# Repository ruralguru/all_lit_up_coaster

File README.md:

# all_lit_up_coaster
LED coaster design,

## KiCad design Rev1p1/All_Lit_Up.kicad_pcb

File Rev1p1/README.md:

# all_lit_up_coaster
LED coaster design.
Created in conjunction with Mad Physist.
Alternating LED design using 555 timer, powered by 4x AAA, Aluminum Can Trigger.
Some moderate soldering required.

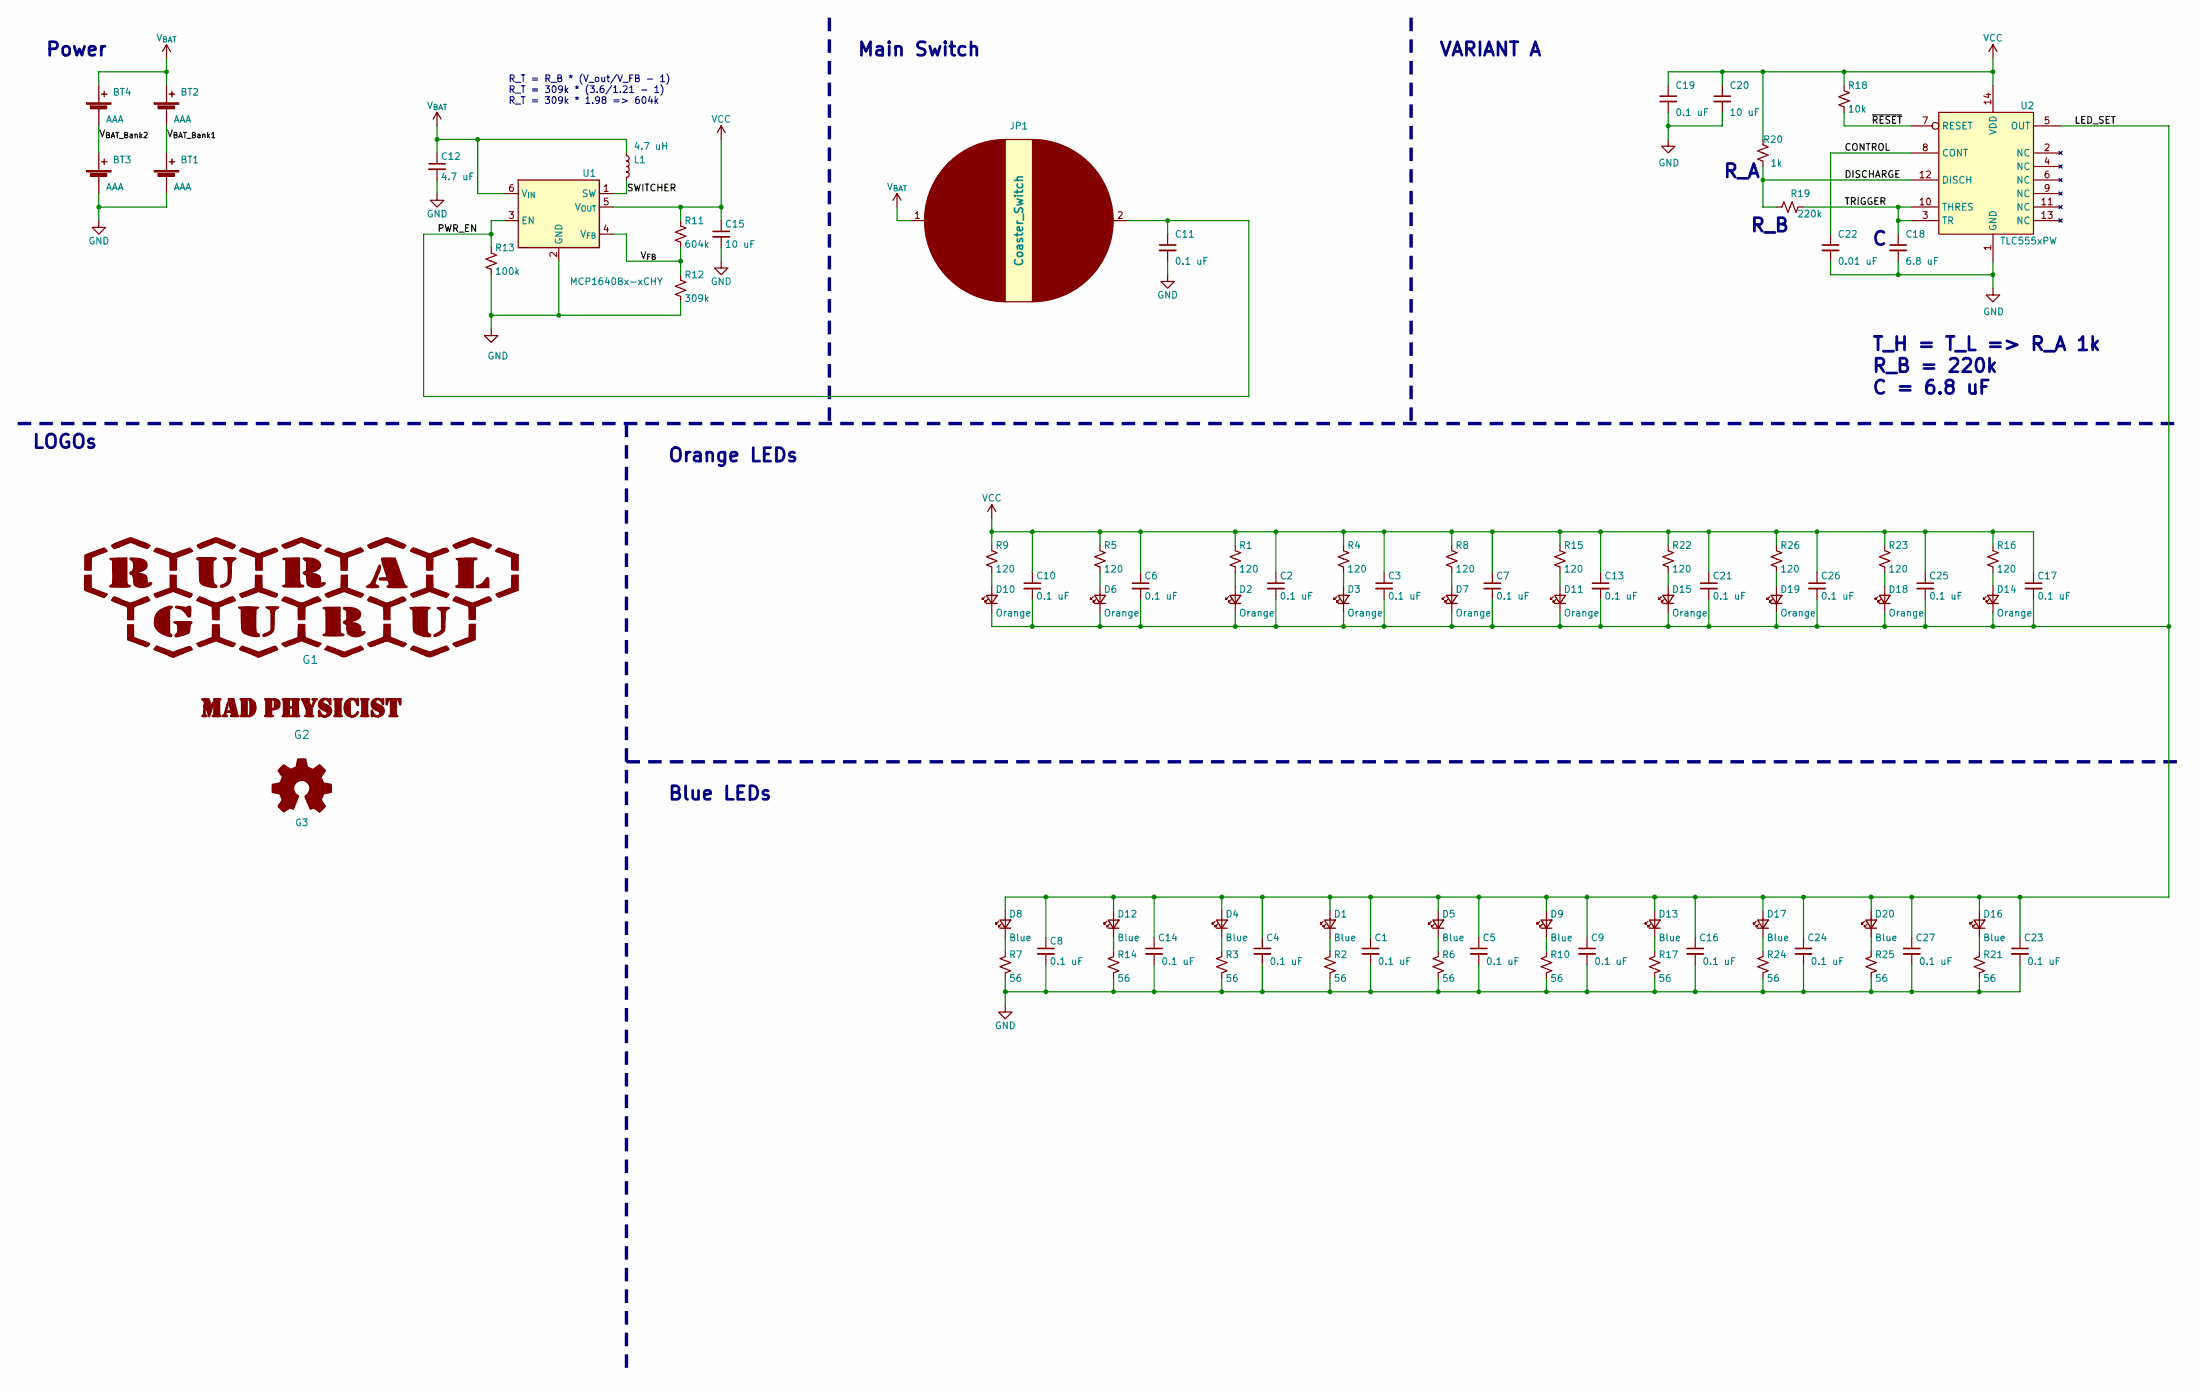
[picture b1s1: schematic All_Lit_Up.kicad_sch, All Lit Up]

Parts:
BT1, BT2, BT3, BT4: AAA; ERW_Battery_Keystone_55(x2)_AAAA; MPN 55 (x2)
C1, C2, C3, C4, C5, C6, C7, C8, C9, C10, C11, C13, C14, C16, C17, C19, C21, C23, C24, C25, C26, C27: 0.1 uF; C_0603_1608Metric; MPN CL10B104KA8NNNC
C12: 4.7 uF; C_0603_1608Metric; MPN GRM188Z71A475ME15D
C15, C20: 10 uF; C_0603_1608Metric; MPN GRM188Z71A106KA73D
C18: 6.8 uF; C_0603_1608Metric; MPN C1608X7S0J685K080AC
C22: 0.01 uF; C_0603_1608Metric; MPN C1608C0G1E103J080AA
D1, D4, D5, D8, D9, D12, D13, D16, D17, D20: Blue; LED_0603_1608Metric; MPN E1221NB--05D000814U1930
D2, D3, D6, D7, D10, D11, D14, D15, D18, D19: Orange; LED_0603_1608Metric; MPN B1911UD--20D001014U1930
G1: LOGO; RuralguruProjects_HEX_2000
G2: Phillip_LOGO; PJ_LOGO_1p5l
G3: Logo_Open_Hardware_Small; OSHW-Symbol_6.7x6mm_SilkScreen
JP1: Coaster_Switch; Coaster_SW
L1: 4.7 uH; L_VLCF4020T; MPN VLCF4020T-4R7N1R2
R1, R4, R5, R8, R9, R15, R16, R22, R23, R26: 120; R_0603_1608Metric; MPN RT0603FRE07120RL
R2, R3, R6, R7, R10, R14, R17, R21, R24, R25: 56; R_0603_1608Metric; MPN RT0603FRE0756RL
R11: 604k; R_0603_1608Metric; MPN RMCF0603FT604K
R12: 309k; R_0603_1608Metric; MPN RMCF0603FT309K
R13: 100k; R_0603_1608Metric; MPN ERJ-3EKF1003V
R18: 10k; R_0603_1608Metric; MPN CRGCQ0603F10K
R19: 220k; R_0603_1608Metric; MPN RMCF0603FT220K
R20: 1k; R_0603_1608Metric; MPN RT0603FRE131KL
U1: MCP1640Bx-xCHY; SOT-23-6; MPN MCP1640BT-I/CHY
U2: TLC555xPW; TSSOP-14_4.4x5mm_P0.65mm; MPN TLC555CPWR

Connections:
/CONTROL: C22.1, U2.8 (CONT)
/DISCHARGE: R19.2, R20.1, U2.12 (DISCH)
/LED_SET: C1.1, C2.2, C3.2, C4.1, C5.1, C6.2, C7.2, C8.1, C9.1, C10.2, C13.2, C14.1, C16.1, C17.2, C21.2, C23.1, C24.1, C25.2, C26.2, C27.1, D1.2 (A), D2.1 (K), D3.1 (K), D4.2 (A), D5.2 (A), D6.1 (K), D7.1 (K), D8.2 (A), D9.2 (A), D10.1 (K), D11.1 (K), D12.2 (A), D13.2 (A), D14.1 (K), D15.1 (K), D16.2 (A), D17.2 (A), D18.1 (K), D19.1 (K), D20.2 (A), U2.5 (OUT)
/PWR_EN: C11.1, JP1.2 (B), R13.1, U1.3 (EN)
/SWITCHER: L1.2, U1.1 (SW)
/TRIGGER: C18.1, R19.1, U2.3 (TR), U2.10 (THRES)
/V_{BAT_Bank1}: BT1.1 (+), BT2.2 (-)
/V_{BAT_Bank2}: BT3.1 (+), BT4.2 (-)
/V_{FB}: R11.2, R12.1, U1.4 (V_{FB})
/~RESET: R18.2, U2.7 (RESET)
GND: BT1.2 (-), BT3.2 (-), C1.2, C4.2, C5.2, C8.2, C9.2, C11.2, C12.2, C14.2, C15.2, C16.2, C18.2, C19.2, C20.2, C22.2, C23.2, C24.2, C27.2, R2.2, R3.2, R6.2, R7.2, R10.2, R12.2, R13.2, R14.2, R17.2, R21.2, R24.2, R25.2, U1.2 (GND), U2.1 (GND)
unnamed: D1.1 (K), R2.1
unnamed: D2.2 (A), R1.2
unnamed: D3.2 (A), R4.2
unnamed: D4.1 (K), R3.1
unnamed: D5.1 (K), R6.1
unnamed: D6.2 (A), R5.2
unnamed: D7.2 (A), R8.2
unnamed: D8.1 (K), R7.1
unnamed: D9.1 (K), R10.1
unnamed: D10.2 (A), R9.2
unnamed: D11.2 (A), R15.2
unnamed: D12.1 (K), R14.1
unnamed: D13.1 (K), R17.1
unnamed: D14.2 (A), R16.2
unnamed: D15.2 (A), R22.2
unnamed: D16.1 (K), R21.1
unnamed: D17.1 (K), R24.1
unnamed: D18.2 (A), R23.2
unnamed: D19.2 (A), R26.2
unnamed: D20.1 (K), R25.1
VCC: C2.1, C3.1, C6.1, C7.1, C10.1, C13.1, C15.1, C17.1, C19.1, C20.1, C21.1, C25.1, C26.1, R1.1, R4.1, R5.1, R8.1, R9.1, R11.1, R15.1, R16.1, R18.1, R20.2, R22.1, R23.1, R26.1, U1.5 (V_{OUT}), U2.14 (VDD)
V_{BAT}: BT2.1 (+), BT4.1 (+), C12.1, JP1.1 (A), L1.1, U1.6 (V_{IN})

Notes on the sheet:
VARIANT A
LOGOs
Blue LEDs
Main Switch
T_H = T_L => R_A 1k R_B = 220k C = 6.8 uF
R_A
R_B
Power
R_T = R_B * (V_out/V_FB - 1) R_T = 309k * (3.6/1.21 - 1) R_T = 309k * 1.98 => 604k
Orange LEDs

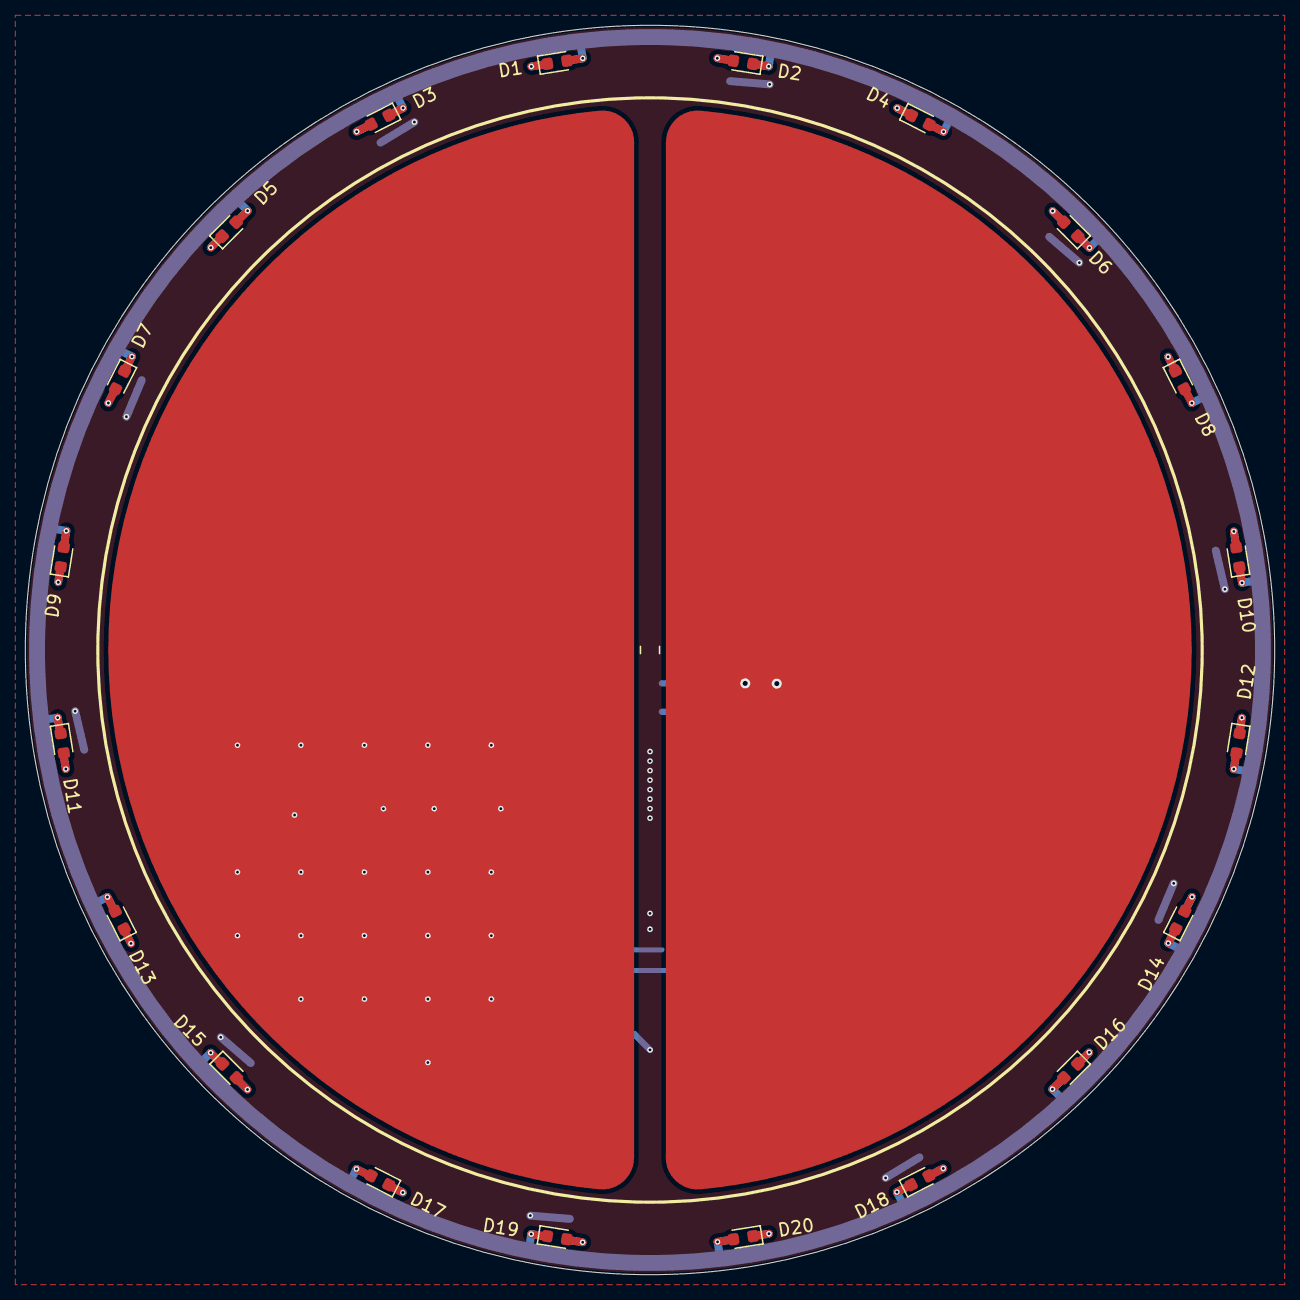
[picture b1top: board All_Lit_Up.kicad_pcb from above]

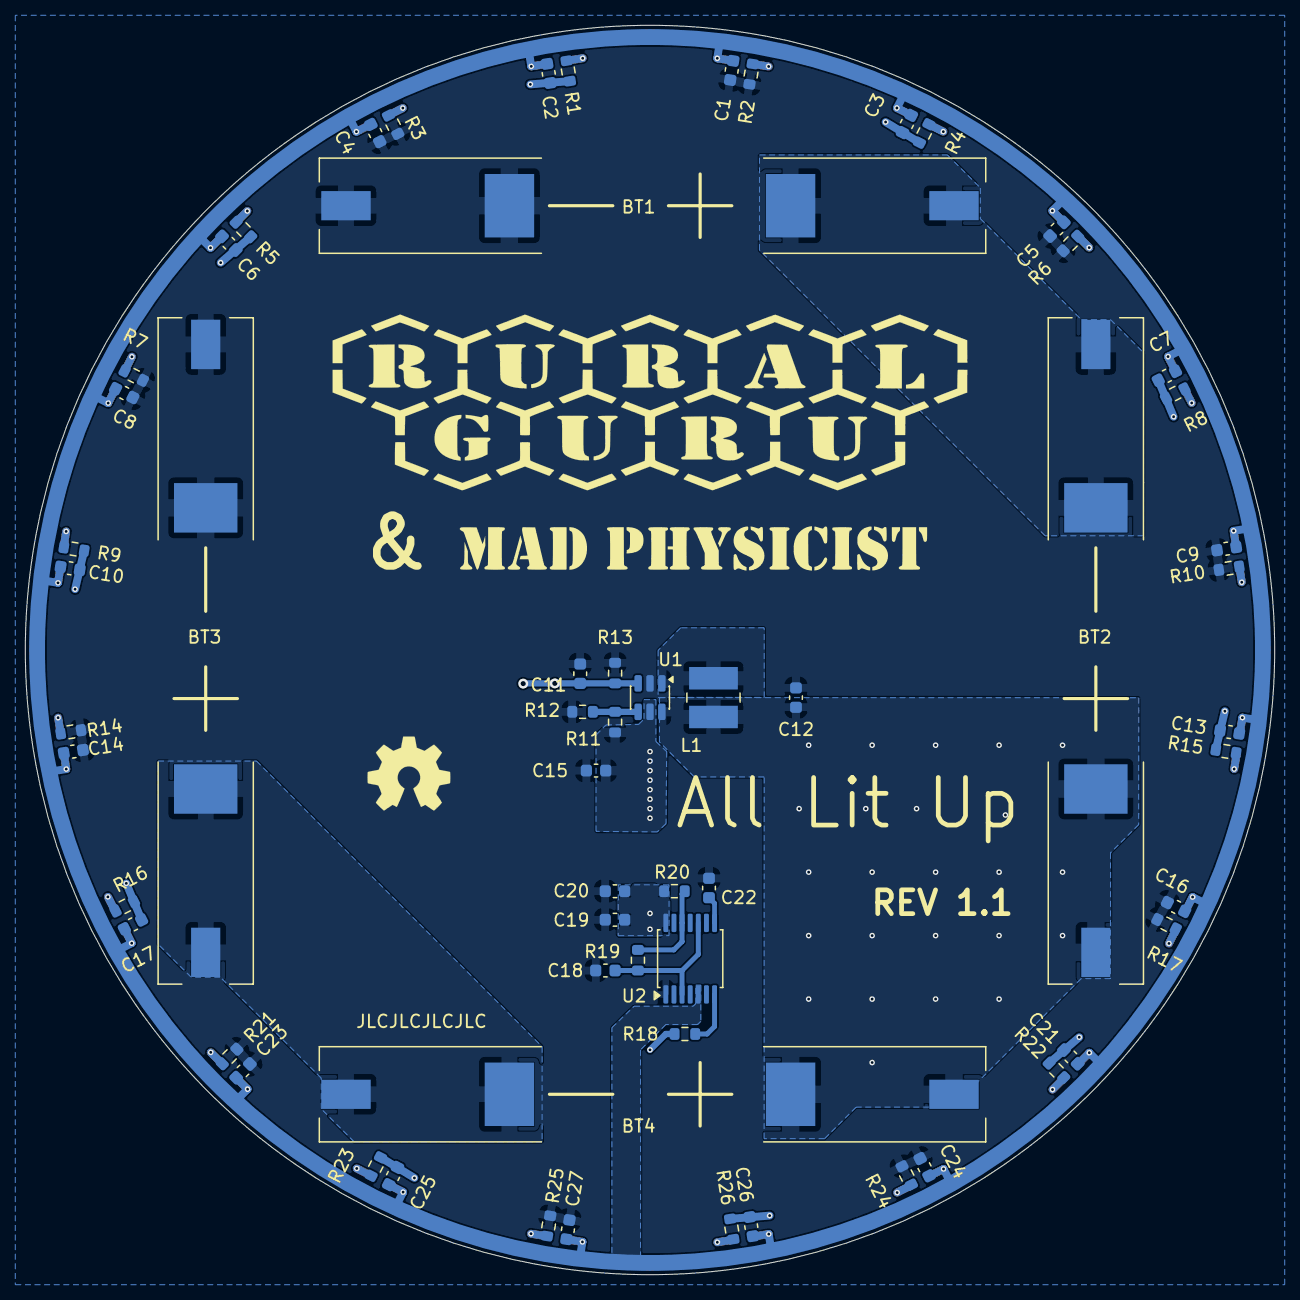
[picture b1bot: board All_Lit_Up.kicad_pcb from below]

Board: 2 copper layers, 100.0 x 100.0 mm, 84 parts (63 on the bottom side), 33 nets.

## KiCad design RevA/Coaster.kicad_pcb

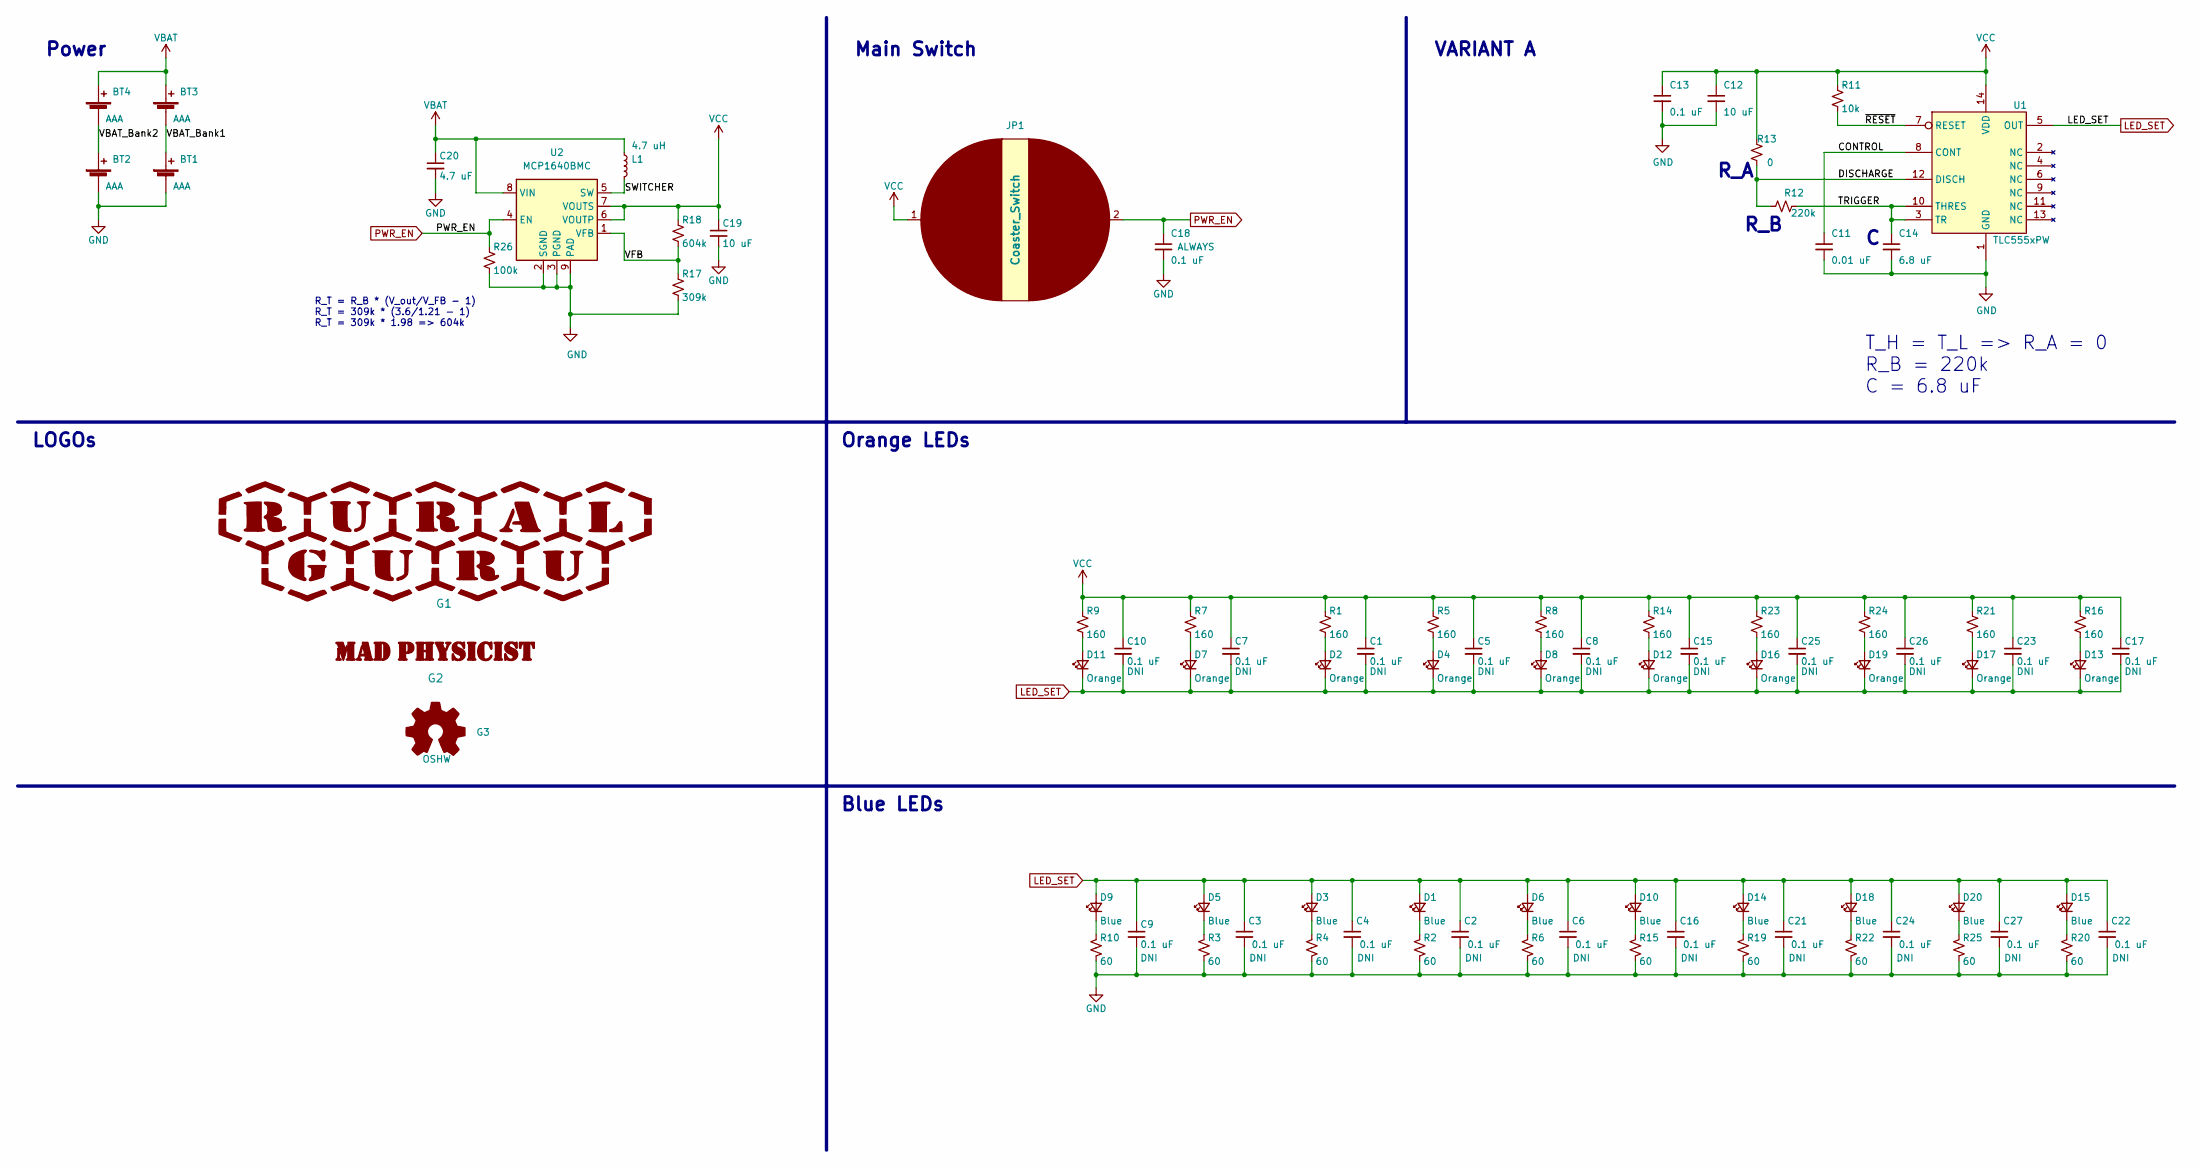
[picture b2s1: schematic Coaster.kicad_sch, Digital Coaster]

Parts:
BT1, BT2, BT3, BT4: AAA; ERW_Battery_Keystone_55(x2)_AAAA; MPN 55
C1, C2, C3, C4, C5, C6, C7, C8, C9, C10, C13, C15, C16, C17, C18, C21, C22, C23, C24, C25, C26, C27: 0.1 uF; C_0603_1608Metric; MPN C0603C104K4NACAUTO
C11: 0.01 uF; C_0603_1608Metric; MPN GRM1885C1H103JA01D
C12: 10 uF; C_0603_1608Metric; MPN CL10B106MQ8NRNC
C14: 6.8 uF; C_0603_1608Metric; MPN C1608X7S0J685M080AC
C19: 10 uF; C_0603_1608Metric; MPN CL10B475KQ8NQNC
C20: 4.7 uF; C_0603_1608Metric; MPN CL10B475KQ8NQNC
D1, D3, D5, D6, D9, D10, D14, D15, D18, D20: Blue; LED_0603_1608Metric; MPN APT1608VBC/D
D2, D4, D7, D8, D11, D12, D13, D16, D17, D19: Orange; LED_0603_1608Metric; MPN AP1608SECK
G1: LOGO; RuralguruProjects_HEX_2000
G2: LOGO; OSHW-LOGO-M
G3: OSHW; OSHW-LOGO-M
JP1: Coaster_Switch; Coaster_SW
L1: 4.7 uH; VLCF4020T-4R7N1R2; MPN 1239AS-H-2R2M=P2
R1, R5, R7, R8, R9, R14, R16, R21, R23, R24: 160; R_0603_1608Metric; MPN RT0805FRE07160RL
R2, R3, R4, R6, R10, R15, R19, R20, R22, R25: 60; R_0603_1608Metric; MPN RT0603FRE0760R4L
R11: 10k; R_0603_1608Metric; MPN RT0603FRE1310KL
R12: 220k; R_0603_1608Metric; MPN RT0603DRE07220KL
R13: 0; R_0603_1608Metric; MPN RC0603FR-070RL
R17: 309k; R_0603_1608Metric; MPN RT0603DRE07100KL
R18: 604k; R_0603_1608Metric; MPN RT0603DRE07357KL
R26: 100k; R_0603_1608Metric; MPN RT0603DRE07100KL
U1: TLC555xPW; TSSOP-14_4.4x5mm_P0.65mm; MPN TLC555CPWRG4
U2: MCP1640BMC; DFN-8-1EP_3x2mm_P0.5mm_EP1.75x1.45mm

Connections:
/CONTROL: C11.1, U1.8 (CONT)
/DISCHARGE: R12.2, R13.1, U1.12 (DISCH)
/SWITCHER: L1.2, U2.5 (SW)
/TRIGGER: C14.1, R12.1, U1.3 (TR), U1.10 (THRES)
/VBAT_Bank1: BT1.1 (+), BT3.2 (-)
/VBAT_Bank2: BT2.1 (+), BT4.2 (-)
/VFB: R17.1, R18.2, U2.1 (VFB)
/~RESET: R11.2, U1.7 (RESET)
GND: BT1.2 (-), BT2.2 (-), C2.2, C3.2, C4.2, C6.2, C9.2, C11.2, C12.2, C13.2, C14.2, C16.2, C18.2, C19.2, C20.2, C21.2, C22.2, C24.2, C27.2, R2.2, R3.2, R4.2, R6.2, R10.2, R15.2, R17.2, R19.2, R20.2, R22.2, R25.2, R26.2, U1.1 (GND), U2.2 (SGND), U2.3 (PGND), U2.9 (PAD)
LED_SET: C1.2, C2.1, C3.1, C4.1, C5.2, C6.1, C7.2, C8.2, C9.1, C10.2, C15.2, C16.1, C17.2, C21.1, C22.1, C23.2, C24.1, C25.2, C26.2, C27.1, D1.2 (A), D2.1 (K), D3.2 (A), D4.1 (K), D5.2 (A), D6.2 (A), D7.1 (K), D8.1 (K), D9.2 (A), D10.2 (A), D11.1 (K), D12.1 (K), D13.1 (K), D14.2 (A), D15.2 (A), D16.1 (K), D17.1 (K), D18.2 (A), D19.1 (K), D20.2 (A), U1.5 (OUT)
unnamed: D1.1 (K), R2.1
unnamed: D2.2 (A), R1.2
unnamed: D3.1 (K), R4.1
unnamed: D4.2 (A), R5.2
unnamed: D5.1 (K), R3.1
unnamed: D6.1 (K), R6.1
unnamed: D7.2 (A), R7.2
unnamed: D8.2 (A), R8.2
unnamed: D9.1 (K), R10.1
unnamed: D10.1 (K), R15.1
unnamed: D11.2 (A), R9.2
unnamed: D12.2 (A), R14.2
unnamed: D13.2 (A), R16.2
unnamed: D14.1 (K), R19.1
unnamed: D15.1 (K), R20.1
unnamed: D16.2 (A), R23.2
unnamed: D17.2 (A), R21.2
unnamed: D18.1 (K), R22.1
unnamed: D19.2 (A), R24.2
unnamed: D20.1 (K), R25.1
PWR_EN: C18.1, JP1.2 (B), R26.1, U2.4 (EN)
VBAT: BT3.1 (+), BT4.1 (+), C20.1, L1.1, U2.8 (VIN)
VCC: C1.1, C5.1, C7.1, C8.1, C10.1, C12.1, C13.1, C15.1, C17.1, C19.1, C23.1, C25.1, C26.1, JP1.1 (A), R1.1, R5.1, R7.1, R8.1, R9.1, R11.1, R13.2, R14.1, R16.1, R18.1, R21.1, R23.1, R24.1, U1.14 (VDD), U2.6 (VOUTP), U2.7 (VOUTS)

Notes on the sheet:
VARIANT A
LOGOs
Blue LEDs
Main Switch
T_H = T_L => R_A = 0 R_B = 220k C = 6.8 uF
R_A
R_B
Power
R_T = R_B * (V_out/V_FB - 1) R_T = 309k * (3.6/1.21 - 1) R_T = 309k * 1.98 => 604k
Orange LEDs

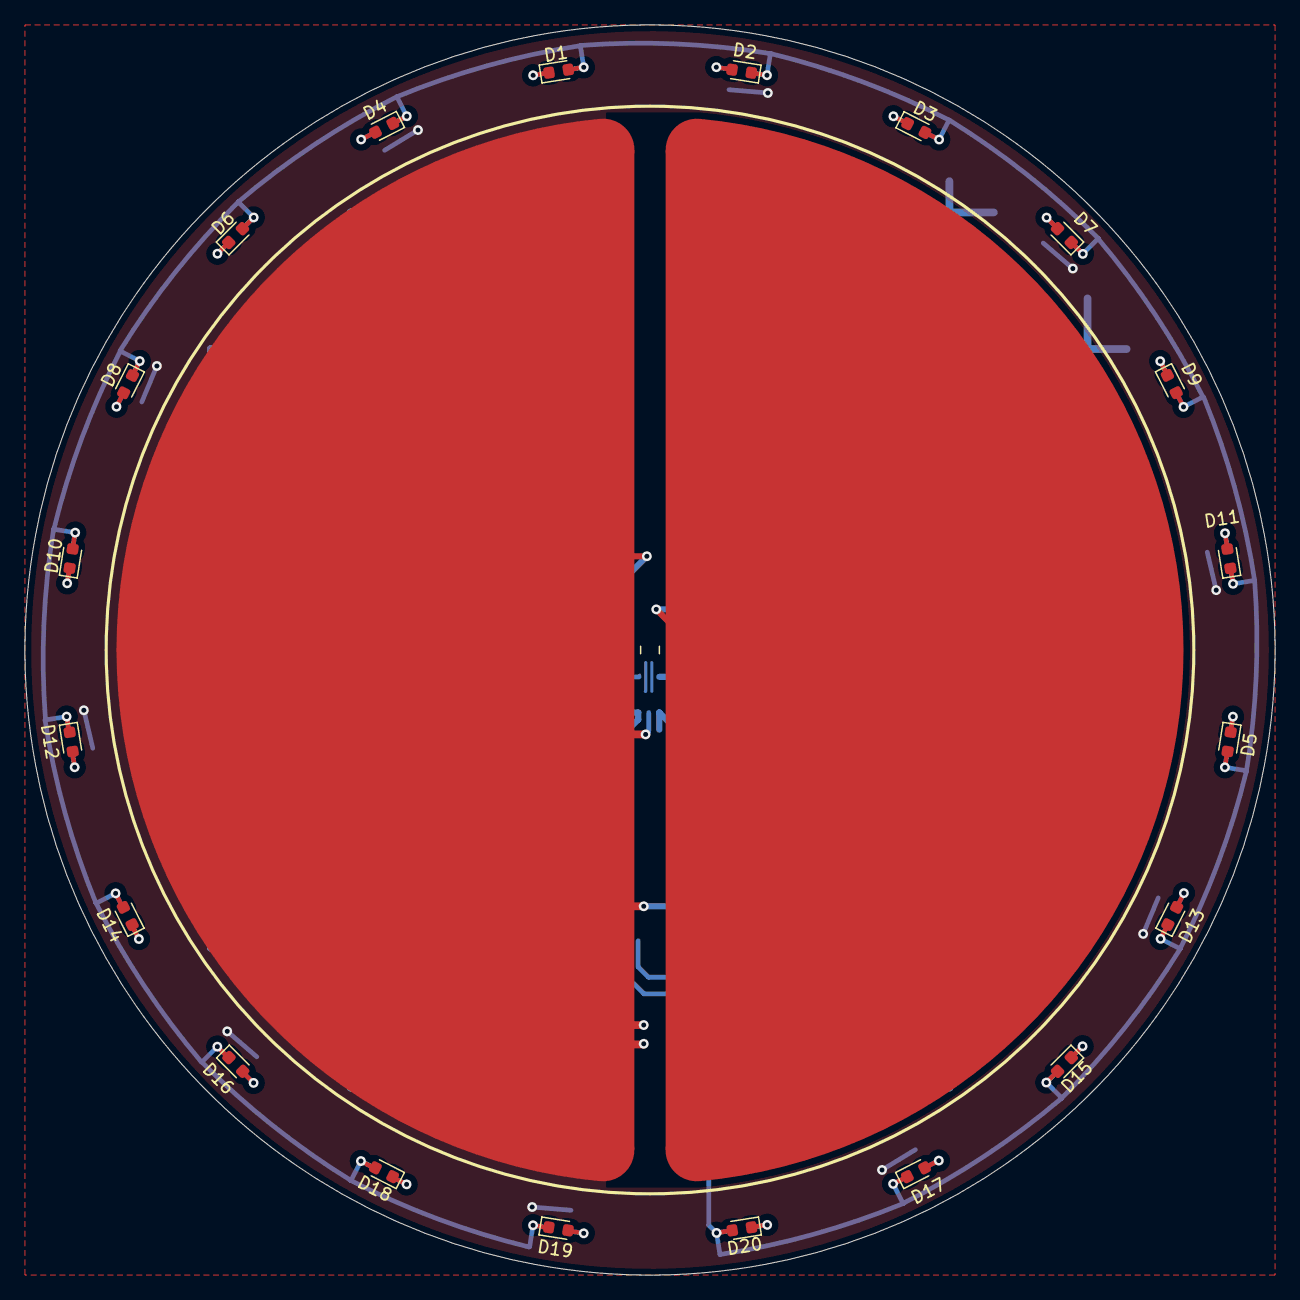
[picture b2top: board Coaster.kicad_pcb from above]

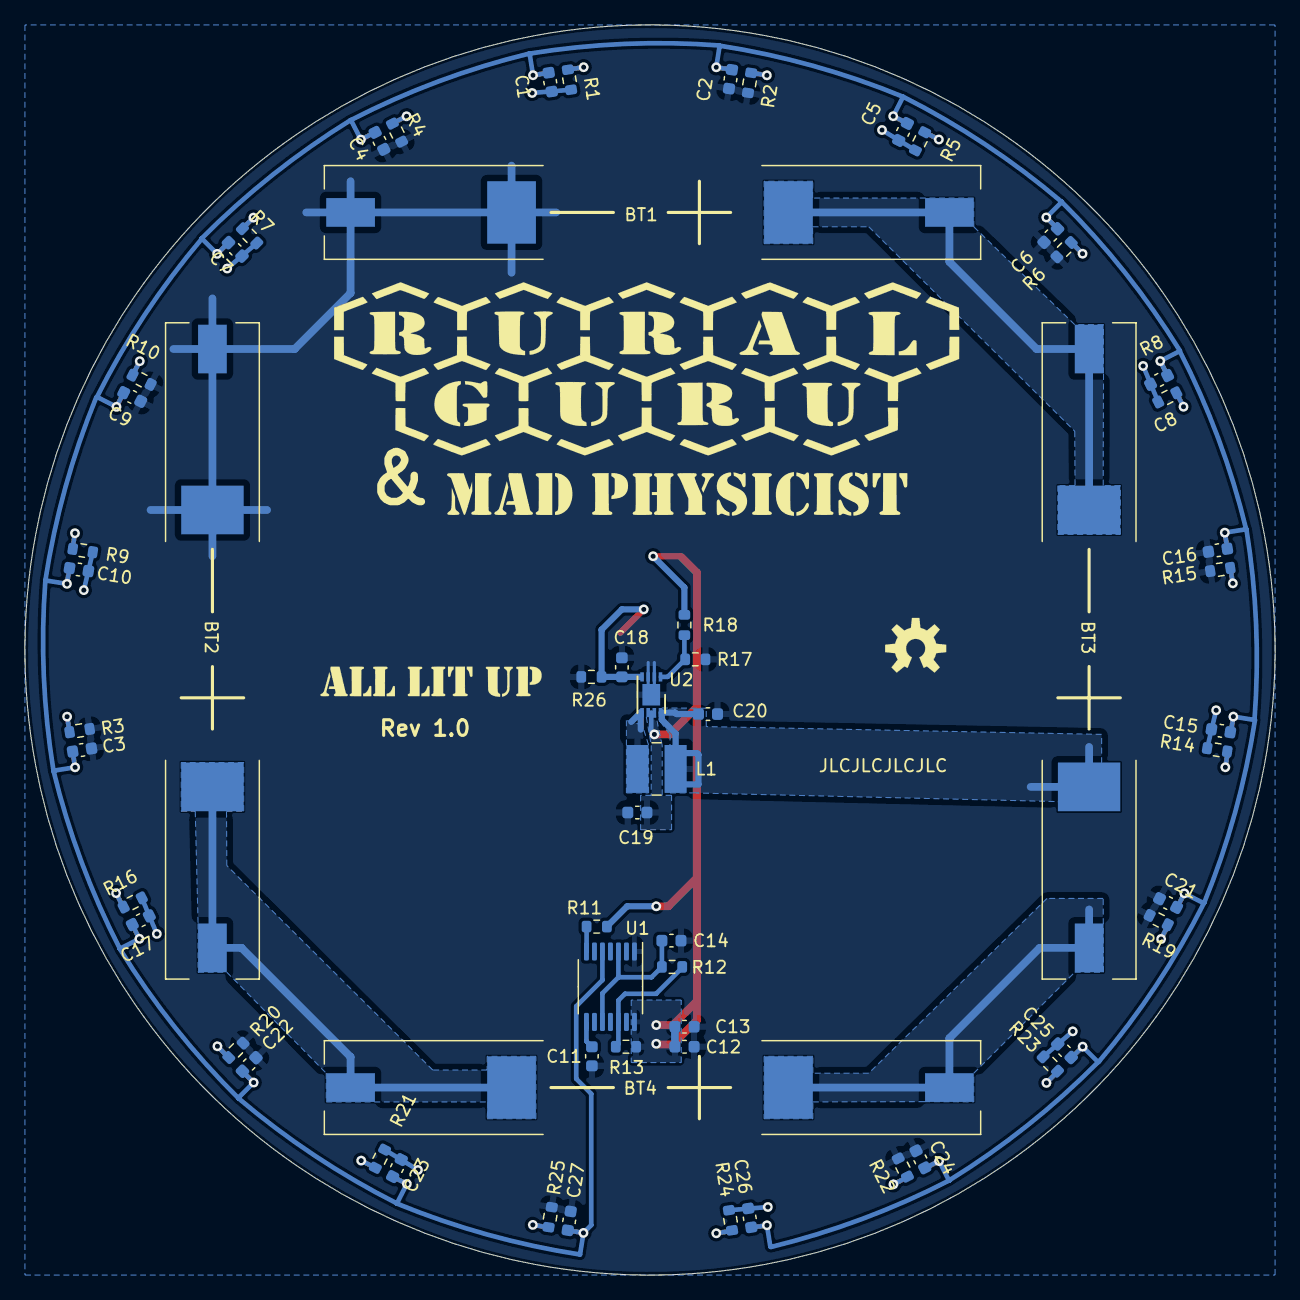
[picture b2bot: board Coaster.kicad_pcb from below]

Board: 2 copper layers, 101.6 x 101.6 mm, 84 parts (63 on the bottom side), 33 nets.

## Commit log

2022-01-22 initial commit with rev 1.0 design
    rev 1.0 commit.
2026-04-27 Rev B Commit
2026-04-27 changed to 1.1 rev
2026-04-27 Improved 1p1 Design
    Cleaned up design, removed DFN for SOIC. added BOM, Schematic, & Step Files. reduced size to 100mm x 100mm. improved traces & Vias.
2026-06-21 Update to working model
    Change LEDs to used Value, Correct to 1k, change resistor values to used. Add LED choice and orientation with silk. correct silk for 1 LED Cap combo. update gbrs. update output documents. Added iBOM
2026-06-21 Update README with project details and requirements
    Added details about the coaster design and its requirements.

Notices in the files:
parts and their libraries:
Copyright 2021 Accelerated Designs. All rights reserved.
